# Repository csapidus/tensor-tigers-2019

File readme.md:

Tensor Tigers is a 501c3 nonprofit organization dedicated to supporting STEM education for K-12 and undergraduate students through the development of autonomous soapbox cars. Our vehicle raced and placed first on 2 November 2019 at Google's Georgia Gravity Games, in the autonomous division. 

Video: 
Raceday: https://www.youtube.com/watch?v=WTvcPwLUy6M 
Cone detection: https://www.youtube.com/watch?v=bC2tEqV1wOY

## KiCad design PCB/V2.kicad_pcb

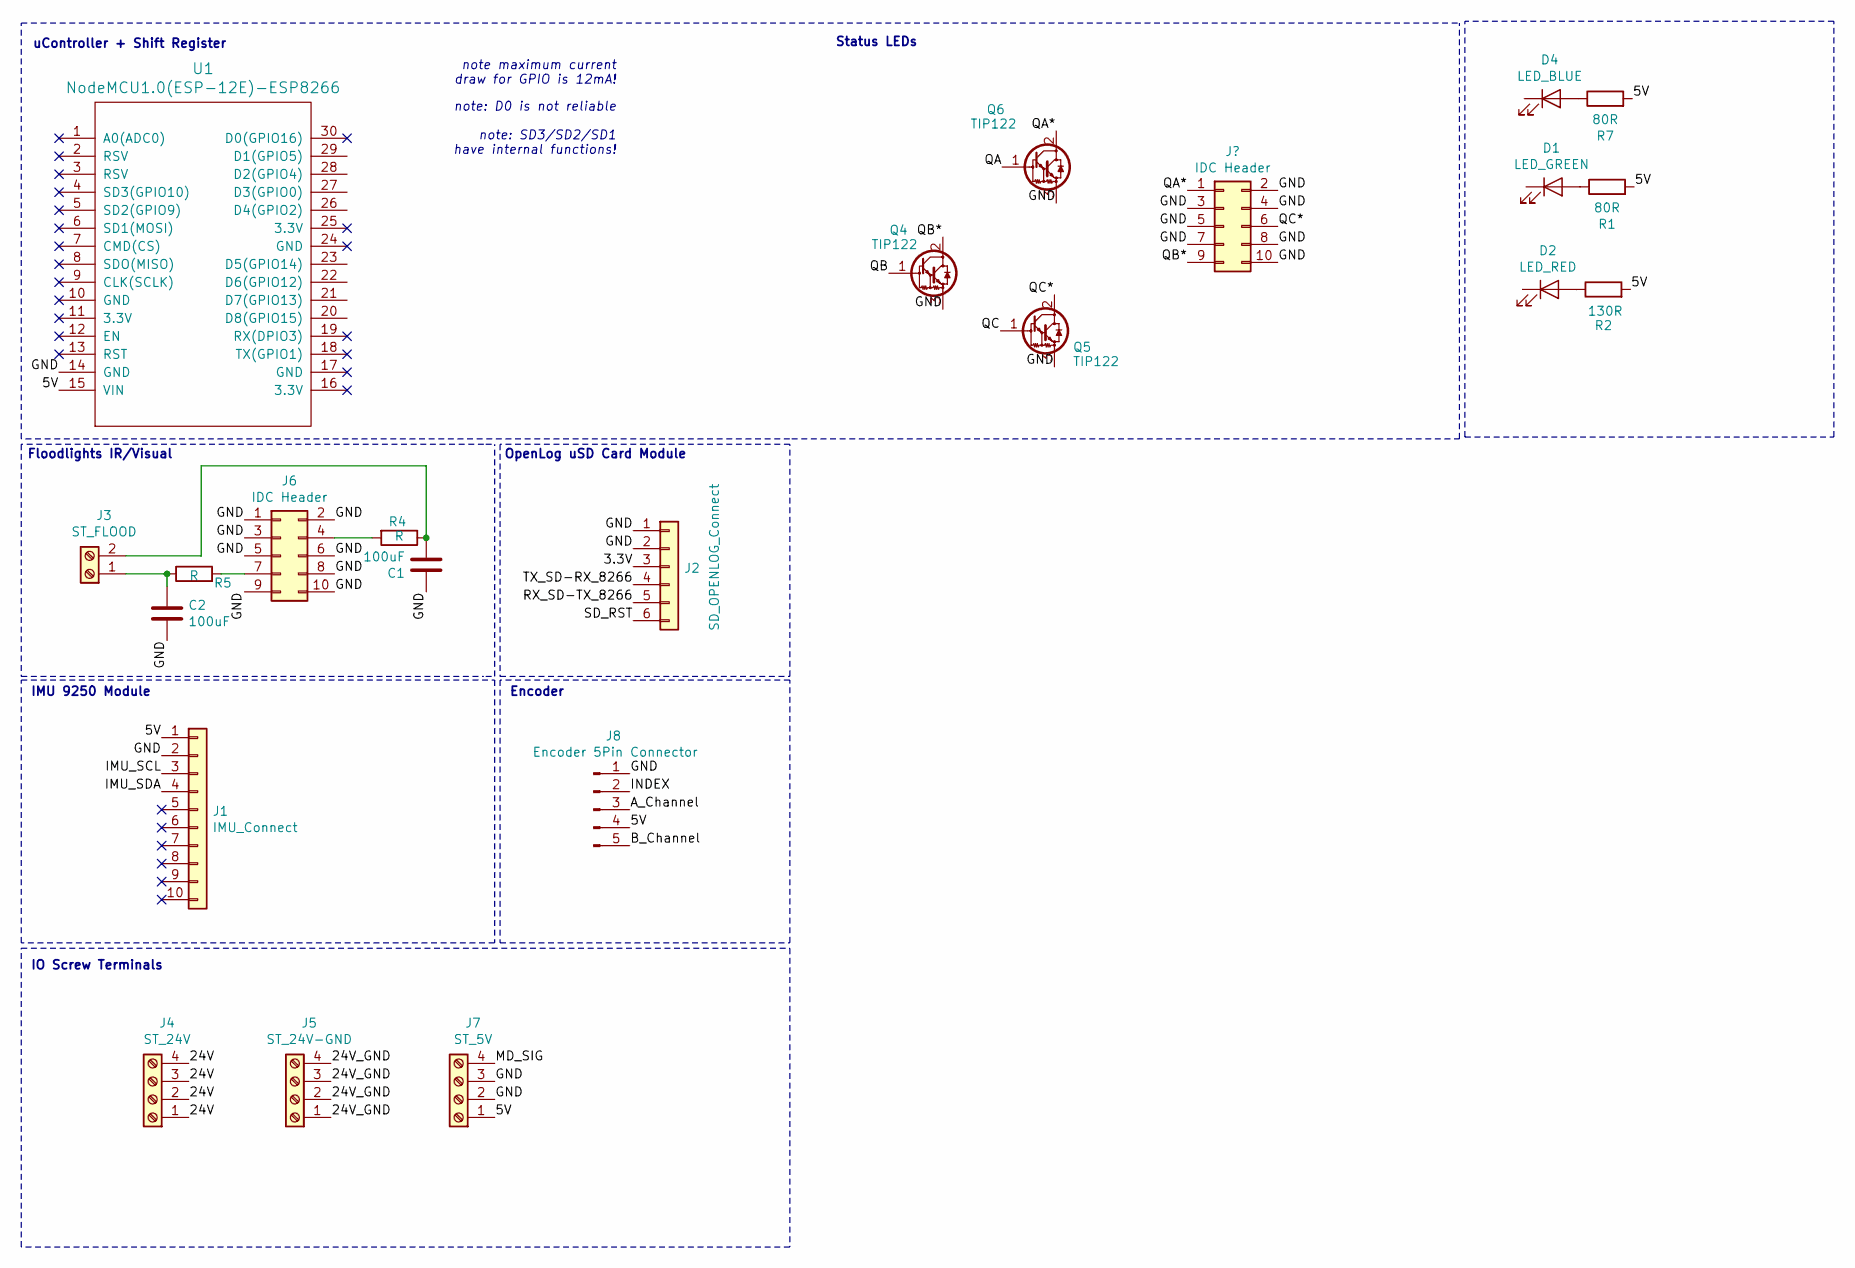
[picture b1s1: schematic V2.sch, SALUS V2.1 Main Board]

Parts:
C1, C2: 100uF; CP_Radial_D8.0mm_P3.50mm
D1: LED_GREEN; LED_D5.0mm
D2: LED_RED; LED_D5.0mm
D4: LED_BLUE; LED_D5.0mm
J1: IMU_Connect; PinHeader_1x10_P2.54mm_Vertical
J2: SD_OPENLOG_Connect; PinHeader_1x06_P2.54mm_Vertical
J3: ST_FLOOD; TerminalBlock_bornier-2_P5.08mm
J4: ST_24V; TerminalBlock_bornier-4_P5.08mm
J5: ST_24V-GND; TerminalBlock_bornier-4_P5.08mm
J6: IDC Header; IDC-Header_2x05_P2.54mm_Vertical
J7: ST_5V; TerminalBlock_bornier-4_P5.08mm
J8: Encoder 5Pin Connector; PinHeader_1x05_P2.54mm_Vertical
Q4, Q5, Q6: TIP122; TO-220-3_Vertical
R1, R7: 80R; R_1206_3216Metric_Pad1.42x1.75mm_HandSolder
R2: 130R; R_1206_3216Metric_Pad1.42x1.75mm_HandSolder
R4, R5: R; R_2512_6332Metric_Pad1.52x3.35mm_HandSolder
U1: NodeMCU1.0(ESP-12E)-ESP8266; NodeMCU1.0(LUA)

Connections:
/3.3V: J2.3; also elsewhere on the board
/5V: J1.1, J7.1, J8.4, R1.2, R2.2, R7.2, U1.15 (VIN); also elsewhere on the board
/24V: J4.1, J4.2, J4.3, J4.4
/24V_GND: J5.1, J5.2, J5.3, J5.4
/A_Channel: J8.3; also elsewhere on the board
/B_Channel: J8.5; also elsewhere on the board
/GND: C1.1, C2.2, J1.2, J2.1, J2.2, J6.1, J6.2, J6.3, J6.5, J6.6, J6.8, J6.9, J6.10, J7.2, J7.3, J8.1, Q4.3 (E), Q5.3 (E), Q6.3 (E), U1.14 (GND); also elsewhere on the board
/IMU_SCL: J1.3, U1.29 (D1(GPIO5))
/IMU_SDA: J1.4, U1.28 (D2(GPIO4))
/INDEX: J8.2; also elsewhere on the board
/MD_SIG: J7.4, U1.27 (D3(GPIO0))
/QA: Q6.1 (B); also elsewhere on the board
/QB: Q4.1 (B); also elsewhere on the board
/QC: Q5.1 (B); also elsewhere on the board
/RX_8266-TX_NANO: U1.21 (D7(GPIO13)); also elsewhere on the board
/RX_SD-TX_8266: J2.5, U1.23 (D5(GPIO14))
/SD_RST: J2.6, U1.22 (D6(GPIO12))
/TX_8266-RX_NANO: U1.20 (D8(GPIO15)); also elsewhere on the board
/TX_SD-RX_8266: J2.4, U1.26 (D4(GPIO2))
unnamed: C1.2, J3.2, R4.1
unnamed: C2.1, J3.1, R5.1
unnamed: D1.1 (K), Q4.2 (C)
unnamed: D1.2 (A), R1.1
unnamed: D2.1 (K), Q5.2 (C)
unnamed: D2.2 (A), R2.1
unnamed: D4.1 (K), Q6.2 (C)
unnamed: D4.2 (A), R7.1
unnamed: J6.4, R4.2
unnamed: J6.7, R5.2

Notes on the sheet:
Floodlights IR/Visual
IMU 9250 Module
OpenLog uSD Card Module
uController + Shift Register
note: SD3/SD2/SD1 have internal functions!
note maximum current draw for GPIO is 12mA!
Status LEDs
note: D0 is not reliable
IO Screw Terminals
Encoder

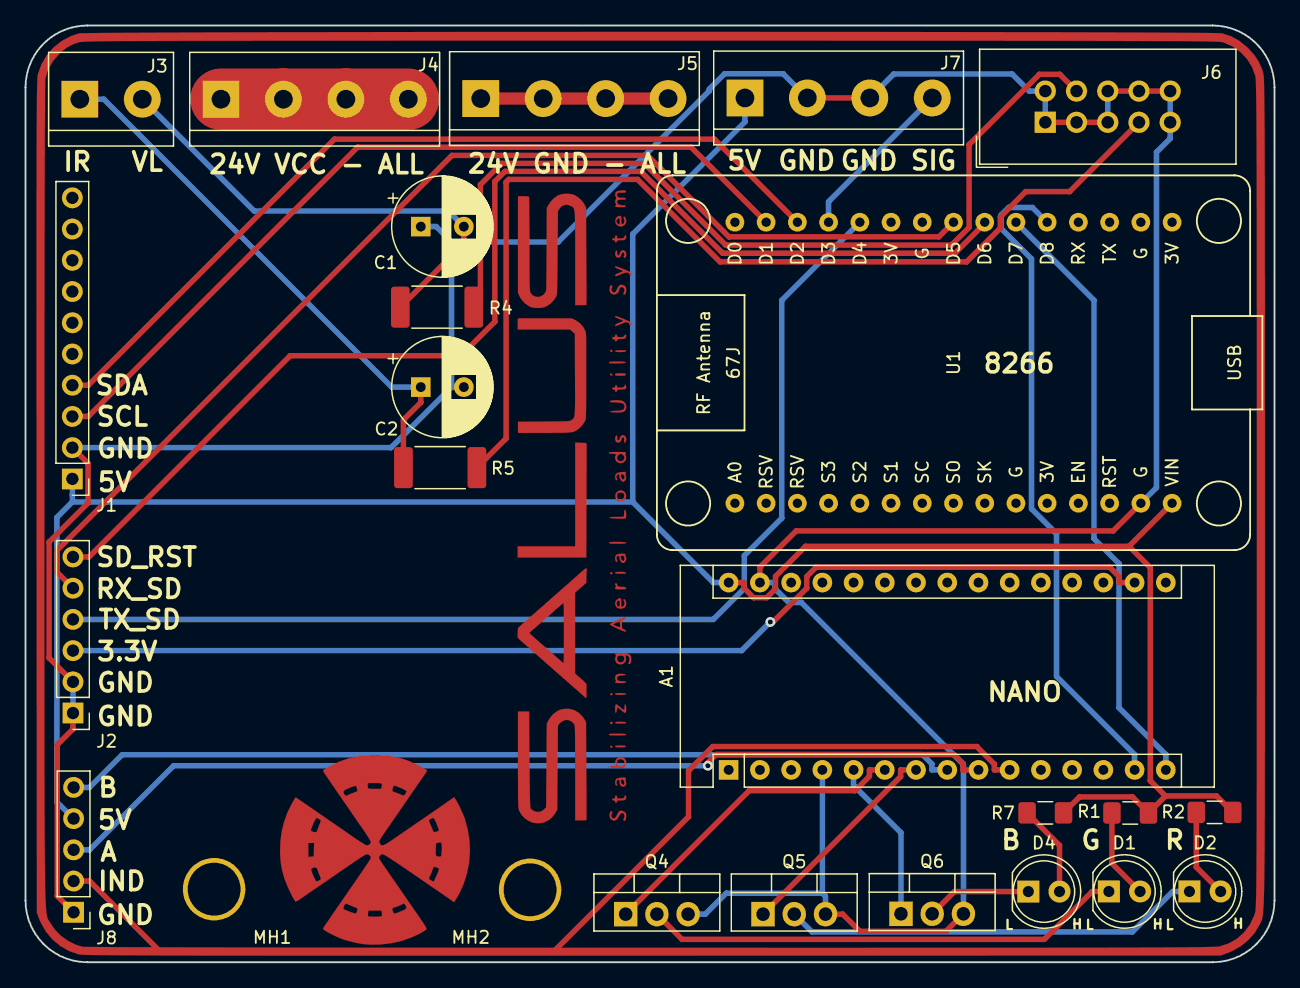
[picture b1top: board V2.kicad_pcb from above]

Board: 2 copper layers, 101.6 x 76.2 mm, 31 parts (0 on the bottom side), 29 nets.

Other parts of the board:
A1: Arduino_Nano_v3.x; Arduino_Nano
GA1: LOGO; trim_main
GA2: LOGO; trim_main_CU
GB1: LOGO; SALUS_STAR_FSM
GB2: LOGO; SALUS_STAR_FCU
LOGO1: LOGO; SALUS_TITLE
LOGO2: LOGO; SALUS_TITLE_CU
MH1, MH2: MountingHole_4.3mm_M4

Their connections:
/3.3V: A1.17; also elsewhere on the board
/5V: A1.30; also elsewhere on the board
/A_Channel: A1.9; also elsewhere on the board
/B_Channel: A1.8; also elsewhere on the board
/GND: A1.4, A1.29; also elsewhere on the board
/INDEX: A1.10; also elsewhere on the board
/QA: A1.5; also elsewhere on the board
/QB: A1.6; also elsewhere on the board
/QC: A1.7; also elsewhere on the board
/RX_8266-TX_NANO: A1.15; also elsewhere on the board
/TX_8266-RX_NANO: A1.14; also elsewhere on the board

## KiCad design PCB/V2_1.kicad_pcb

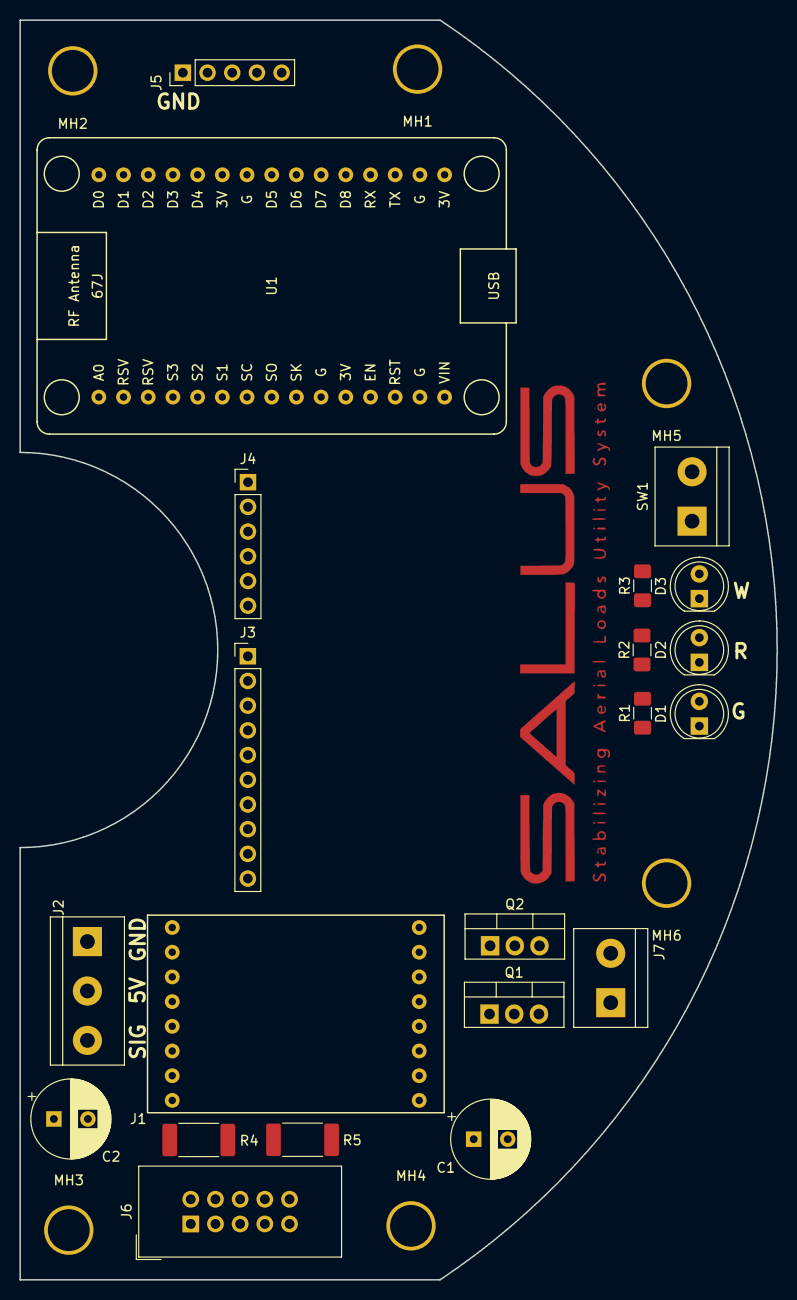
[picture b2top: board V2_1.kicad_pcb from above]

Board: 2 copper layers, 77.9 x 129.5 mm, 29 parts (0 on the bottom side), 28 nets, no tracks yet.

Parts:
C1, C2: 100uF; CP_Radial_D8.0mm_P3.50mm
D1: LED_GREEN; LED_D5.0mm
D2: LED_RED; LED_D5.0mm
D3: LED_WHITE; LED_D5.0mm
J1: RFM_Module_Connect
J2: Screw_Terminal_IO; TerminalBlock_bornier-3_P5.08mm
J3: IMU_Connect; PinHeader_1x10_P2.54mm_Vertical
J4: SD_OPENLOG_Connect; PinHeader_1x06_P2.54mm_Vertical
J5: E6_Optical_Encoder_Connect; PinHeader_1x05_P2.54mm_Vertical
J6: IDC Header; IDC-Header_2x05_P2.54mm_Vertical
J7: TEST; TerminalBlock_bornier-2_P5.08mm
LOGO1: LOGO; SALUS_TITLE
LOGO2: LOGO; SALUS_TITLE_CU
MH1, MH2, MH3, MH4, MH5, MH6: MountingHole_4.3mm_M4
Q1, Q2: TIP122; TO-220-3_Vertical
R1: 80R; R_1206_3216Metric_Pad1.42x1.75mm_HandSolder
R2: 130R; R_1206_3216Metric_Pad1.42x1.75mm_HandSolder
R3: 85R; R_1206_3216Metric_Pad1.42x1.75mm_HandSolder
R4, R5: R; R_2512_6332Metric_Pad1.52x3.35mm_HandSolder
SW1: SW_SPST; TerminalBlock_bornier-2_P5.08mm
U1: NodeMCU1.0(ESP-12E)-ESP8266; NodeMCU1.0(LUA)

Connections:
/3.3V: J1.8, J4.3, U1.16
/5V: C1.2, C2.1, J2.2, J3.1, J5.4, R4.1, R5.1, SW1.2, U1.15
/A_Channel: J5.3, U1.28
/B_Channel: J5.5, U1.27
/GND: C1.1, C2.2, D1.1, D2.1, D3.1, J1.7, J2.1, J3.2, J4.1, J4.2, J5.1, J5.2, J6.2, J6.4, J6.5, J6.6, J6.8, J6.10, Q1.3, Q2.3, U1.14
/IR: Q1.1, U1.26
/MD_SIG: J2.3, U1.30
/RFM_InterruptD: J1.6, U1.29
/RFM_MISO: J1.1, U1.8
/RFM_MOSI: J1.2, U1.6
/RFM_SCK: J1.3, U1.9
/RFM_SS: J1.4, U1.7
/RST: J4.6, U1.13
/SD_RX: J4.4, U1.19
/SD_TX: J4.5, U1.18
/Visual: Q2.1, U1.23
unnamed: D1.2, R1.2
unnamed: D2.2, R2.2
unnamed: D3.2, R3.2
unnamed: J6.1, Q1.2
unnamed: J6.3, R4.2
unnamed: J6.7, Q2.2
unnamed: J6.9, R5.2
unnamed: J7.1, U1.5
unnamed: J7.2, U1.4
unnamed: R1.1, U1.21
unnamed: R2.1, U1.20
unnamed: R3.1, U1.22

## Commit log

2019-11-26 added readme.md
2019-12-08 added catalog
